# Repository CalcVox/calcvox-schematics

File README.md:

# calcvox-schematics

Working directory of the CalcVox Project Schematics. These are KiCAD files and should be able to be opened on the newest version.

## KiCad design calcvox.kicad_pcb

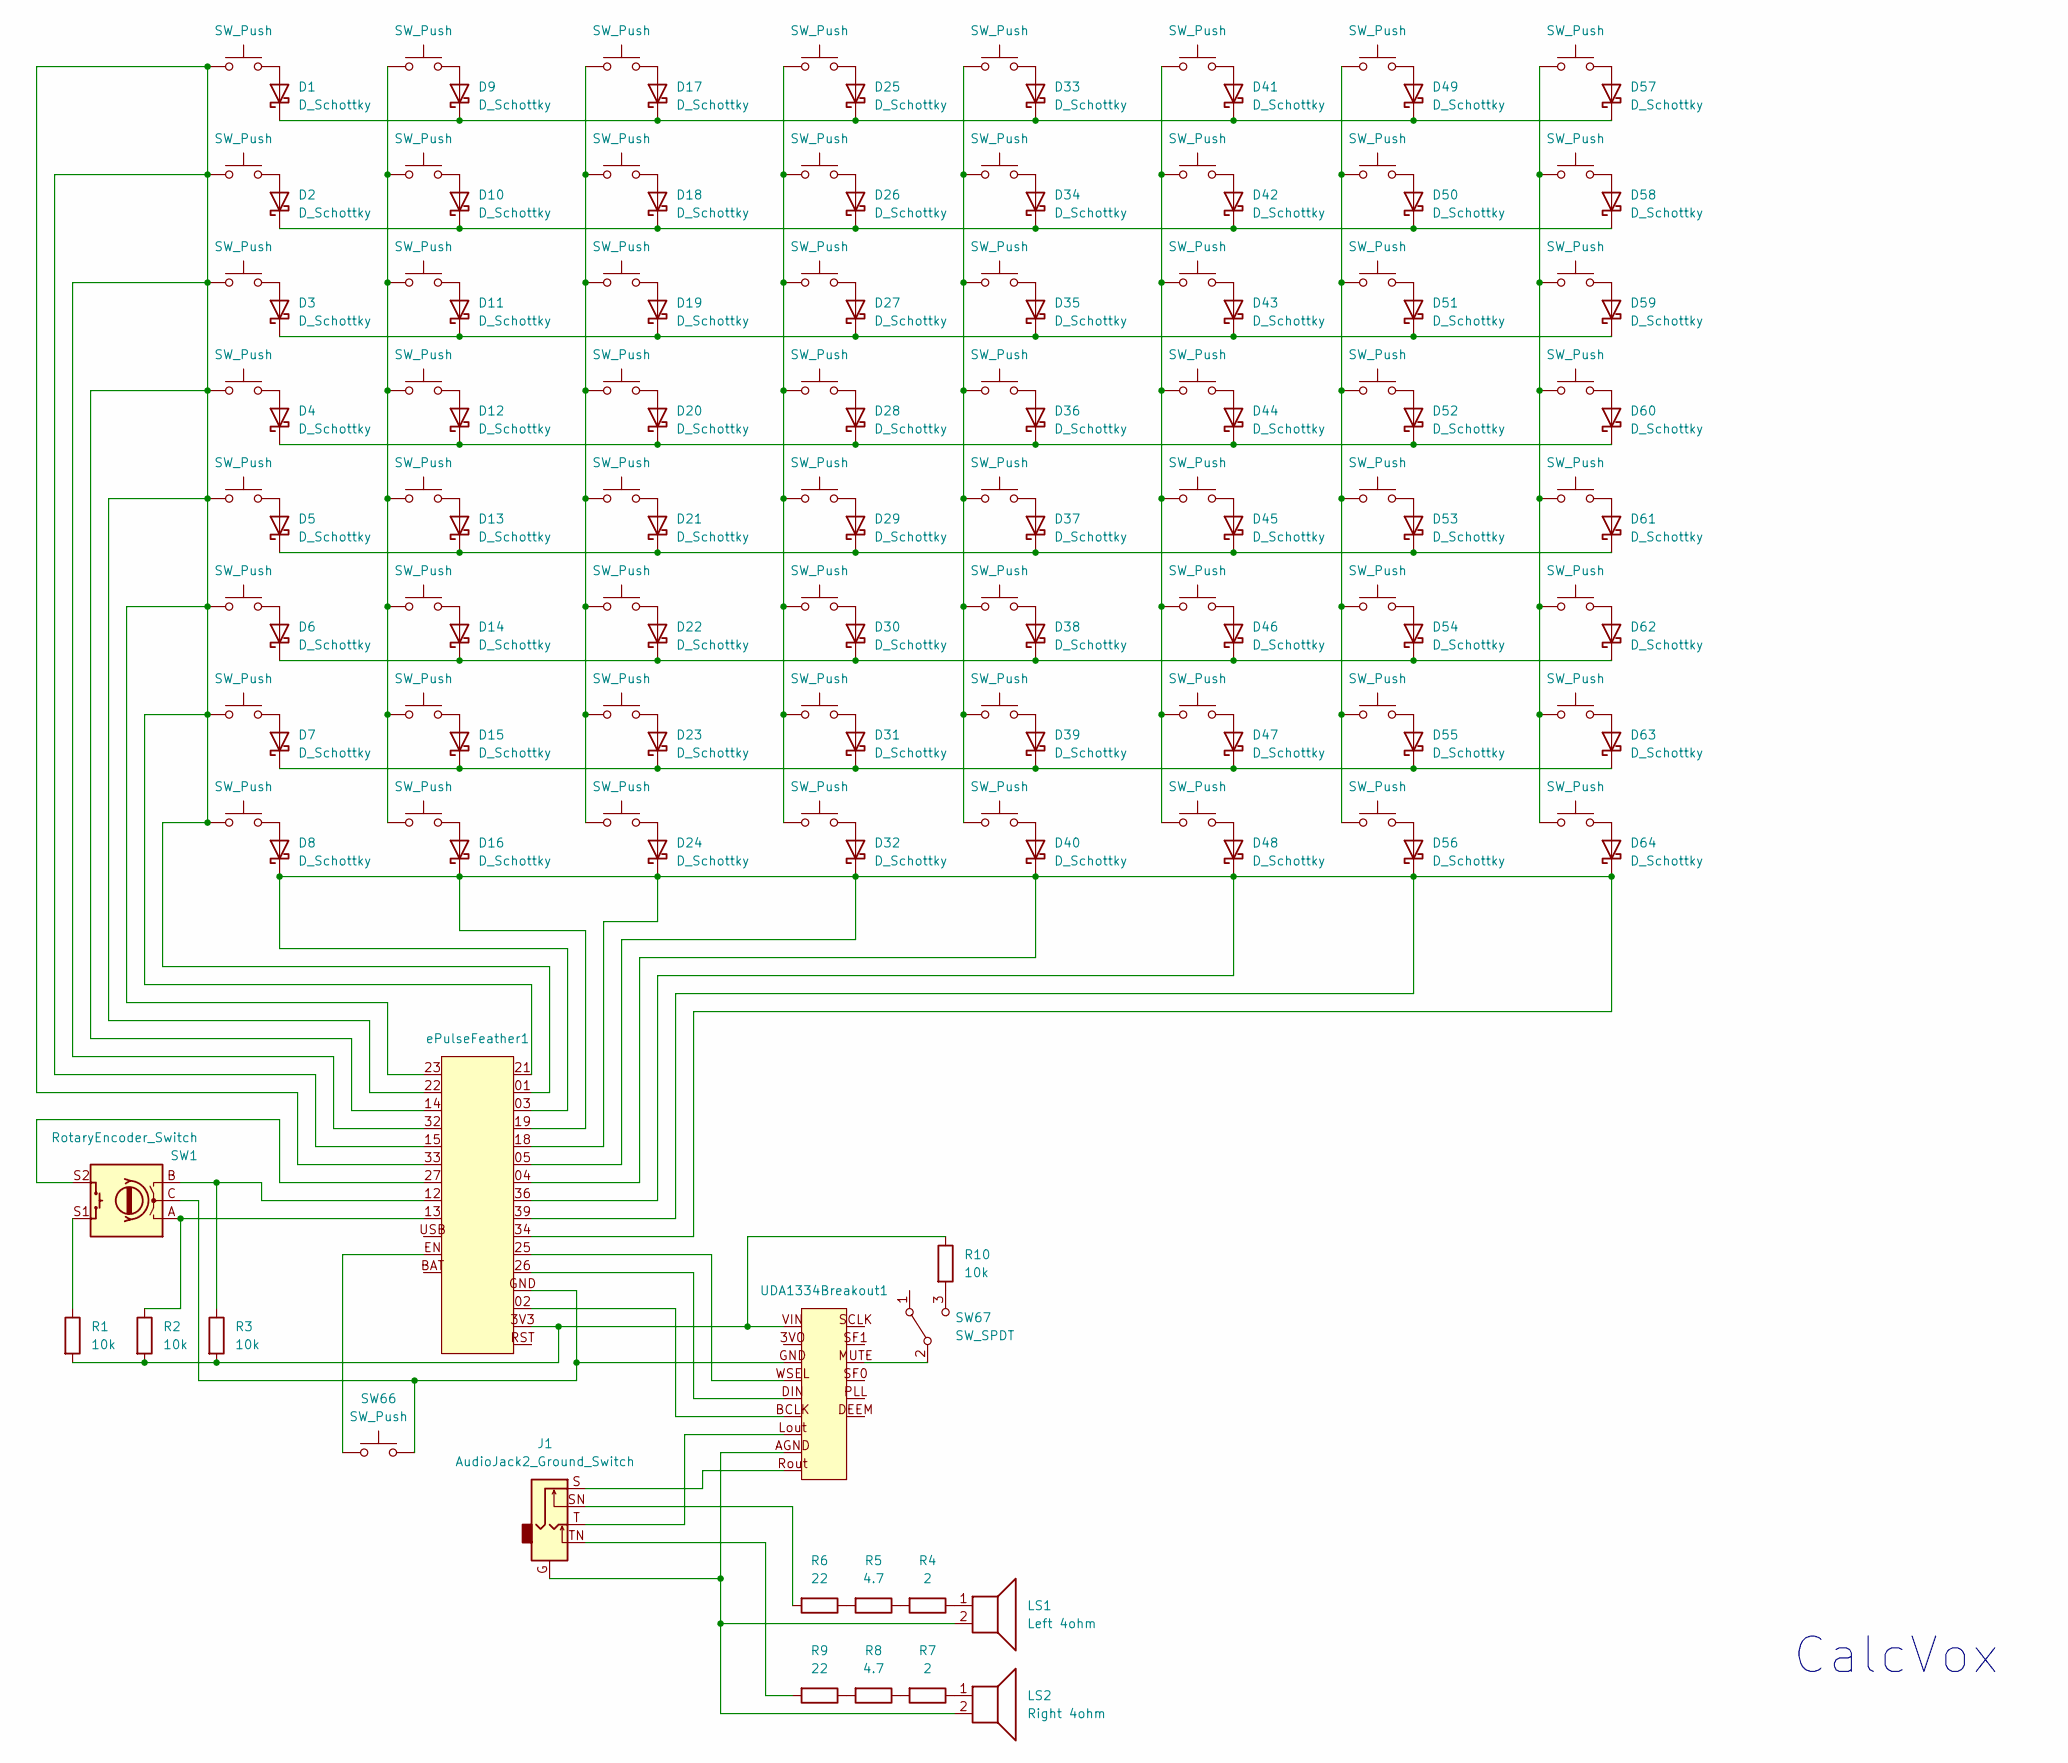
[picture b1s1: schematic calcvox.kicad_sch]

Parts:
D1, D2, D3, D4, D5, D6, D7, D8, D9, D10, D11, D12, D13, D14, D15, D16, D17, D18, D19, D20, D21, D22, D23, D24, D25, D26, D27, D28, D29, D30, D31, D32, D33, D34, D35, D36, D37, D38, D39, D40, D41, D42, D43, D44, D45, D46, D47, D48, D49, D50, D51, D52, D53, D54, D55, D56, D57, D58, D59, D60, D61, D62, D63, D64: D_Schottky; D_A-405_P12.70mm_Horizontal
J1: AudioJack2_Ground_Switch; Jack_3.5mm_CUI_SJ1-3525N_Horizontal
LS1: Left 4ohm; speaker mount
LS2: Right 4ohm; speaker mount
R1, R2, R3, R10: 10k; R_Axial_DIN0207_L6.3mm_D2.5mm_P7.62mm_Horizontal
R4, R7: 2; R_Axial_DIN0207_L6.3mm_D2.5mm_P7.62mm_Horizontal
R5, R8: 4.7; R_Axial_DIN0207_L6.3mm_D2.5mm_P7.62mm_Horizontal
R6, R9: 22; R_Axial_DIN0207_L6.3mm_D2.5mm_P7.62mm_Horizontal
SW1: RotaryEncoder_Switch; SF-ROTARY-ENCODER
SW2, SW3, SW4, SW5, SW6, SW7, SW8, SW9, SW10, SW11, SW12, SW13, SW14, SW15, SW16, SW17, SW18, SW19, SW20, SW21, SW22, SW23, SW24, SW25, SW26, SW27, SW28, SW29, SW30, SW31, SW32, SW33, SW34, SW35, SW36, SW37, SW38, SW39, SW40, SW41, SW42, SW43, SW44, SW45, SW46, SW47, SW48, SW49, SW50, SW51, SW52, SW53, SW54, SW55, SW56, SW57, SW58, SW59, SW60, SW61, SW62, SW63, SW64, SW65, SW66: SW_Push; SW_PUSH_6mm_H8.5mm
SW67: SW_SPDT; SW_Slide_1P2T_CK_OS102011MS2Q
UDA1334Breakout1: UDA1334 Breakout
ePulseFeather1: ePulse Feather

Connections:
unnamed: D1.2 (A), SW2.2
unnamed: D1.1 (K), D9.1 (K), D17.1 (K), D25.1 (K), D33.1 (K), D41.1 (K), D49.1 (K), D57.1 (K)
unnamed: D2.2 (A), SW3.2
unnamed: D3.2 (A), SW4.2
unnamed: D4.2 (A), SW5.2
unnamed: D5.2 (A), SW6.2
unnamed: D6.2 (A), SW7.2
unnamed: D7.2 (A), SW8.2
unnamed: D8.2 (A), SW9.2
unnamed: D9.2 (A), SW10.2
unnamed: D10.2 (A), SW11.2
unnamed: D2.1 (K), D10.1 (K), D18.1 (K), D26.1 (K), D34.1 (K), D42.1 (K), D50.1 (K), D58.1 (K)
unnamed: D11.2 (A), SW12.2
unnamed: D3.1 (K), D11.1 (K), D19.1 (K), D27.1 (K), D35.1 (K), D43.1 (K), D51.1 (K), D59.1 (K)
unnamed: D12.2 (A), SW13.2
unnamed: D4.1 (K), D12.1 (K), D20.1 (K), D28.1 (K), D36.1 (K), D44.1 (K), D52.1 (K), D60.1 (K)
unnamed: D13.2 (A), SW14.2
unnamed: D5.1 (K), D13.1 (K), D21.1 (K), D29.1 (K), D37.1 (K), D45.1 (K), D53.1 (K), D61.1 (K)
unnamed: D14.2 (A), SW15.2
unnamed: D6.1 (K), D14.1 (K), D22.1 (K), D30.1 (K), D38.1 (K), D46.1 (K), D54.1 (K), D62.1 (K)
unnamed: D15.2 (A), SW16.2
unnamed: D7.1 (K), D15.1 (K), D23.1 (K), D31.1 (K), D39.1 (K), D47.1 (K), D55.1 (K), D63.1 (K)
unnamed: D16.2 (A), SW17.2
unnamed: D8.1 (K), D16.1 (K), D24.1 (K), D32.1 (K), D40.1 (K), D48.1 (K), D56.1 (K), D64.1 (K), ePulseFeather1.03, ePulseFeather1.04, ePulseFeather1.05, ePulseFeather1.18, ePulseFeather1.19, ePulseFeather1.34, ePulseFeather1.36, ePulseFeather1.39
unnamed: D17.2 (A), SW18.2
unnamed: D18.2 (A), SW19.2
unnamed: D19.2 (A), SW20.2
unnamed: D20.2 (A), SW21.2
unnamed: D21.2 (A), SW22.2
unnamed: D22.2 (A), SW23.2
unnamed: D23.2 (A), SW24.2
unnamed: D24.2 (A), SW25.2
unnamed: D25.2 (A), SW26.2
unnamed: D26.2 (A), SW27.2
unnamed: D27.2 (A), SW28.2
unnamed: D28.2 (A), SW29.2
unnamed: D29.2 (A), SW30.2
unnamed: D30.2 (A), SW31.2
unnamed: D31.2 (A), SW32.2
unnamed: D32.2 (A), SW33.2
unnamed: D33.2 (A), SW34.2
unnamed: D34.2 (A), SW35.2
unnamed: D35.2 (A), SW36.2
unnamed: D36.2 (A), SW37.2
unnamed: D37.2 (A), SW38.2
unnamed: D38.2 (A), SW39.2
unnamed: D39.2 (A), SW40.2
unnamed: D40.2 (A), SW41.2
unnamed: D41.2 (A), SW42.2
unnamed: D42.2 (A), SW43.2
unnamed: D43.2 (A), SW44.2
unnamed: D44.2 (A), SW45.2
unnamed: D45.2 (A), SW46.2
unnamed: D46.2 (A), SW47.2
unnamed: D47.2 (A), SW48.2
unnamed: D48.2 (A), SW49.2
unnamed: D49.2 (A), SW50.2
unnamed: D50.2 (A), SW51.2
unnamed: D51.2 (A), SW52.2
unnamed: D52.2 (A), SW53.2
unnamed: D53.2 (A), SW54.2
unnamed: D54.2 (A), SW55.2
unnamed: D55.2 (A), SW56.2
unnamed: D56.2 (A), SW57.2
unnamed: D57.2 (A), SW58.2
unnamed: D58.2 (A), SW59.2
unnamed: D59.2 (A), SW60.2
unnamed: D60.2 (A), SW61.2
unnamed: D61.2 (A), SW62.2
unnamed: D62.2 (A), SW63.2
unnamed: D63.2 (A), SW64.2
unnamed: D64.2 (A), SW65.2
unnamed: J1.G, LS1.2, LS2.2, UDA1334Breakout1.AGND
unnamed: J1.S, UDA1334Breakout1.Rout
unnamed: J1.SN, R6.2
unnamed: J1.T, UDA1334Breakout1.Lout
unnamed: J1.TN, R9.2
unnamed: LS1.1, R4.1
unnamed: LS2.1, R7.1
unnamed: R1.1, SW1.S1
unnamed: R1.2, R2.2, R3.2, R10.1, UDA1334Breakout1.VIN, ePulseFeather1.3V3
unnamed: R2.1, SW1.A, ePulseFeather1.13
unnamed: R3.1, SW1.B, ePulseFeather1.12
unnamed: R4.2, R5.1
unnamed: R5.2, R6.1
unnamed: R7.2, R8.1
unnamed: R8.2, R9.1
unnamed: SW1.C, SW66.2, UDA1334Breakout1.GND, ePulseFeather1.GND
unnamed: SW1.S2, ePulseFeather1.27
unnamed: SW2.1, SW3.1, SW4.1, SW5.1, SW6.1, SW7.1, SW8.1, SW9.1, ePulseFeather1.01, ePulseFeather1.14, ePulseFeather1.15, ePulseFeather1.21, ePulseFeather1.22, ePulseFeather1.23, ePulseFeather1.32, ePulseFeather1.33
unnamed: SW10.1, SW11.1, SW12.1, SW13.1, SW14.1, SW15.1, SW16.1, SW17.1
unnamed: SW18.1, SW19.1, SW20.1, SW21.1, SW22.1, SW23.1, SW24.1, SW25.1
unnamed: SW26.1, SW27.1, SW28.1, SW29.1, SW30.1, SW31.1, SW32.1, SW33.1
unnamed: SW34.1, SW35.1, SW36.1, SW37.1, SW38.1, SW39.1, SW40.1, SW41.1
unnamed: SW42.1, SW43.1, SW44.1, SW45.1, SW46.1, SW47.1, SW48.1, SW49.1
unnamed: SW50.1, SW51.1, SW52.1, SW53.1, SW54.1, SW55.1, SW56.1, SW57.1
unnamed: SW58.1, SW59.1, SW60.1, SW61.1, SW62.1, SW63.1, SW64.1, SW65.1
unnamed: SW66.1, ePulseFeather1.EN
unnamed: SW67.2 (B), UDA1334Breakout1.MUTE
unnamed: R10.2, SW67.3 (C)
unnamed: UDA1334Breakout1.BCLK, ePulseFeather1.02
unnamed: UDA1334Breakout1.DIN, ePulseFeather1.26
unnamed: UDA1334Breakout1.WSEL, ePulseFeather1.25

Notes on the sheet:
CalcVox

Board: 2 copper layers, 146 parts (0 on the bottom side), 103 nets, no tracks yet.

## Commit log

2023-11-17 added gitignore
2023-11-21 added new changes
2023-11-27 updated schematics
